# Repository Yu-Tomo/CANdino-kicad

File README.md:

# CANdino-kicad

CAN用IC搭載のArduino互換機になります。

Qiitaの記事はこちらから→https://qiita.com/Yu-Tomo/items/e30f2b3abf415f76f6f1

※基盤を発注は自己責任でお願いします。

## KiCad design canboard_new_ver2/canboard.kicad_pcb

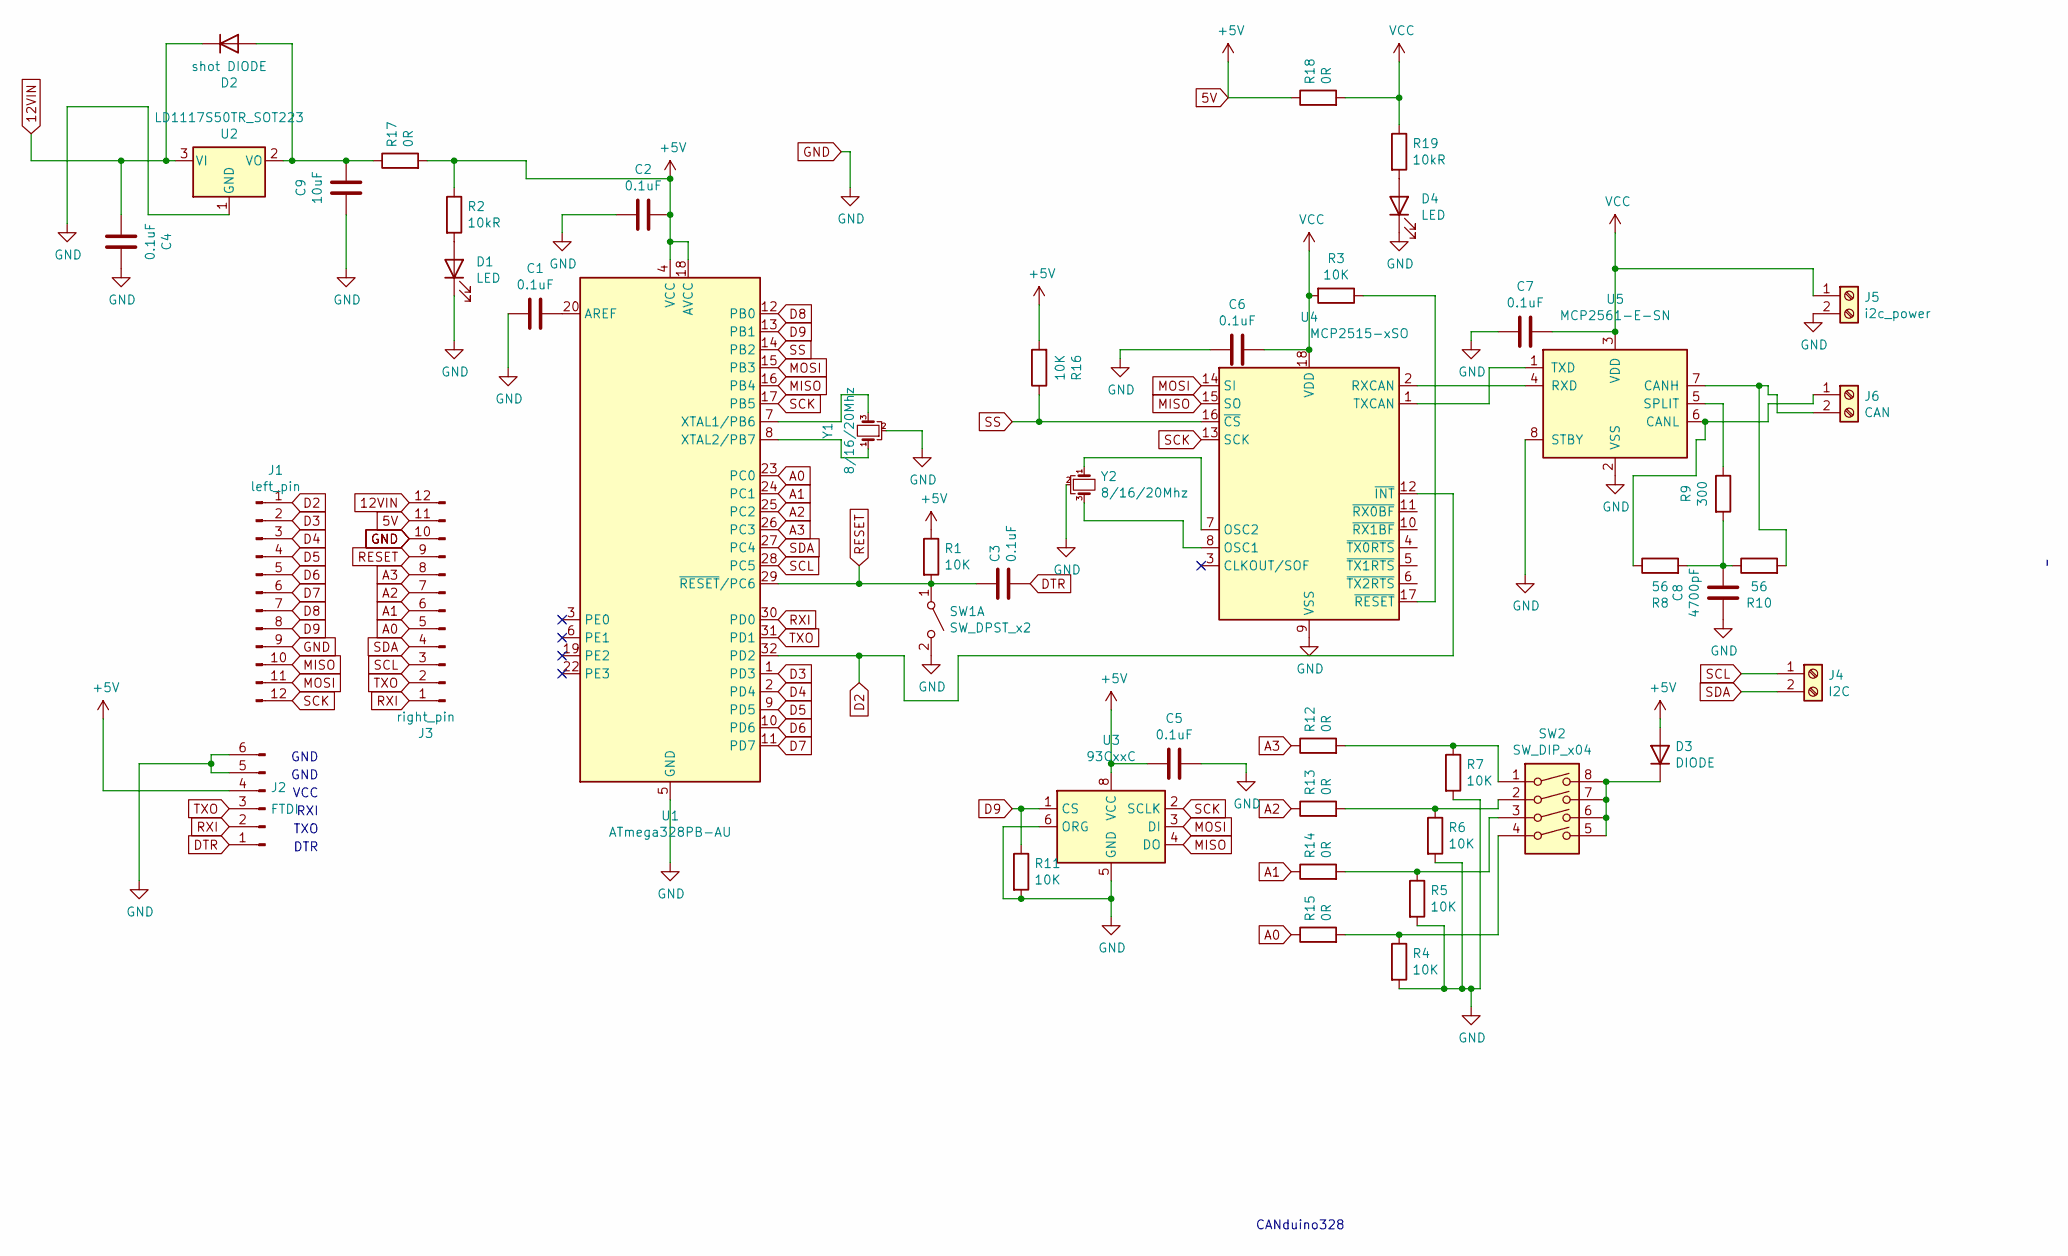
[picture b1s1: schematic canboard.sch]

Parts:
C1, C2, C3, C4, C5, C6, C7: 0.1uF; C_0402_1005Metric
C8: 4700pF; C_0603_1608Metric
C9: 10uF; C_0805_2012Metric
D1, D4: LED; LED_0603_1608Metric
D2: shot DIODE; D_0805_2012Metric
D3: DIODE; D_0805_2012Metric
J1: left_pin; PinHeader_1x12_P2.54mm_Vertical
J2: FTDI; PinHeader_1x06_P2.54mm_Vertical
J3: right_pin; PinHeader_1x12_P2.54mm_Vertical
J4: I2C; TerminalBlock_TE_282834-2_1x02_P2.54mm_Horizontal
J5: i2c_power; TerminalBlock_TE_282834-2_1x02_P2.54mm_Horizontal
J6: CAN; TerminalBlock_TE_282834-2_1x02_P2.54mm_Horizontal
R1, R3, R4, R5, R6, R7, R11, R16: 10K; R_0603_1608Metric
R2, R19: 10kR; R_0603_1608Metric
R8, R10: 56; R_1206_3216Metric
R9: 300; R_0603_1608Metric
R12, R13, R14, R15, R17, R18: 0R; R_0603_1608Metric
SW1: SW_DPST_x2; SW_SPST_REED_CT05-XXXX-J1
SW2: SW_DIP_x04; SW_DIP_SPSTx04_Slide_Copal_CHS-04B_W7.62mm_P1.27mm
U1: ATmega328PB-AU; TQFP-32_7x7mm_P0.8mm
U2: LD1117S50TR_SOT223; SOT-223-3_TabPin2
U3: 93CxxC; DIP-8_W7.62mm_Socket
U4: MCP2515-xSO; SOIC-18W_7.5x11.6mm_P1.27mm
U5: MCP2561-E-SN; SOIC-8_3.9x4.9mm_P1.27mm
Y1, Y2: 8/16/20Mhz; Resonator_SMD_muRata_CSTxExxV-3Pin_3.0x1.1mm_HandSoldering

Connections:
5V: C2.1, C5.2, D3.1 (A), J2.4, J3.11, R1.1, R2.1, R16.2, R17.2, R18.1, U1.4 (VCC), U1.18 (AVCC), U3.8 (VCC)
12VIN: C4.2, D2.2 (K), J3.12, U2.3 (VI)
A0: J3.5, R15.1, U1.23 (PC0)
A1: J3.6, R14.1, U1.24 (PC1)
A2: J3.7, R13.1, U1.25 (PC2)
A3: J3.8, R12.1, U1.26 (PC3)
D2: J1.1, U1.32 (PD2), U4.12 (~INT)
D3: J1.2, U1.1 (PD3)
D4: J1.3, U1.2 (PD4)
D5: J1.4, U1.9 (PD5)
D6: J1.5, U1.10 (PD6)
D7: J1.6, U1.11 (PD7)
D8: J1.7, U1.12 (PB0)
D9: J1.8, R11.1, U1.13 (PB1), U3.1 (CS)
DTR: C3.1, J2.1
GND: C1.2, C2.2, C4.1, C5.1, C6.2, C7.2, C8.2, C9.2, D1.1 (K), D4.1 (K), J1.9, J2.5, J2.6, J3.10, J5.2, R4.2, R5.2, R6.2, R7.2, R11.2, SW1.2 (B), U1.5 (GND), U1.21 (GND), U2.1 (GND), U3.5 (GND), U3.6 (ORG), U4.9 (VSS), U5.2 (VSS), U5.8 (STBY), Y1.2, Y2.2
MISO: J1.10, U1.16 (PB4), U3.4 (DO), U4.15 (SO)
MOSI: J1.11, U1.15 (PB3), U3.3 (DI), U4.14 (SI)
unnamed: C1.1, U1.20 (AREF)
unnamed: C8.1, R8.2, R9.2, R10.1
unnamed: C9.1, D2.1 (A), R17.1, U2.2 (VO)
unnamed: D1.2 (A), R2.2
unnamed: D3.2 (K), SW2.5, SW2.6, SW2.7, SW2.8
unnamed: D4.2 (A), R19.2
unnamed: J6.1, R8.1, U5.6 (CANL)
unnamed: J6.2, R10.2, U5.7 (CANH)
unnamed: R3.1, U4.17 (~RESET)
unnamed: R9.1, U5.5 (SPLIT)
unnamed: R7.1, R12.2, SW2.1
unnamed: R6.1, R13.2, SW2.2
unnamed: R5.1, R14.2, SW2.3
unnamed: R4.1, R15.2, SW2.4
unnamed: U1.7 (XTAL1/PB6), Y1.3
unnamed: U1.8 (XTAL2/PB7), Y1.1
unnamed: U4.1 (TXCAN), U5.1 (TXD)
unnamed: U4.2 (RXCAN), U5.4 (RXD)
unnamed: U4.7 (OSC2), Y2.1
unnamed: U4.8 (OSC1), Y2.3
RESET: C3.2, J3.9, R1.2, SW1.1 (A), U1.29 (~RESET~/PC6)
RXI: J2.2, J3.1, U1.30 (PD0)
SCK: J1.12, U1.17 (PB5), U3.2 (SCLK), U4.13 (SCK)
SCL: J3.3, J4.1, U1.28 (PC5)
SDA: J3.4, J4.2, U1.27 (PC4)
SS: R16.1, U1.14 (PB2), U4.16 (~CS)
TXO: J2.3, J3.2, U1.31 (PD1)
VCC: C6.1, C7.1, J5.1, R3.2, R18.2, R19.1, U4.18 (VDD), U5.3 (VDD)

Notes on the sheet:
GND
VCC
DTR
TXO
RXI
CANduino328

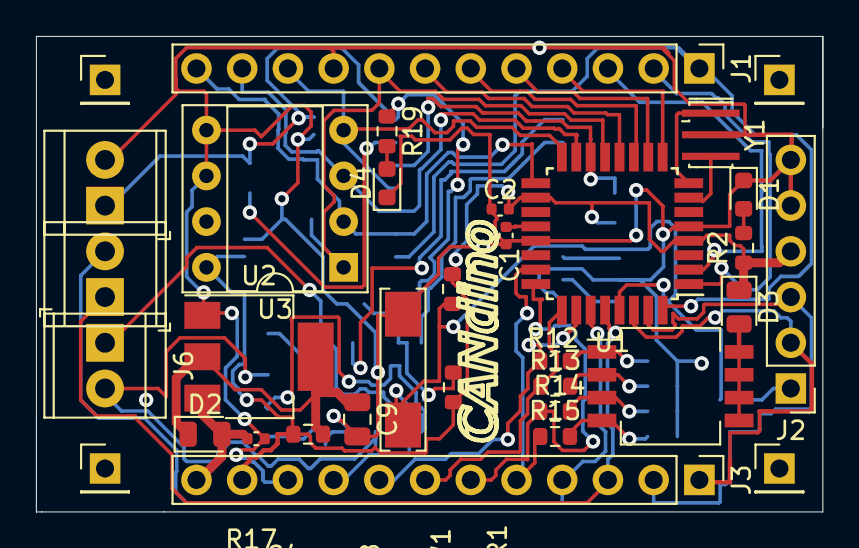
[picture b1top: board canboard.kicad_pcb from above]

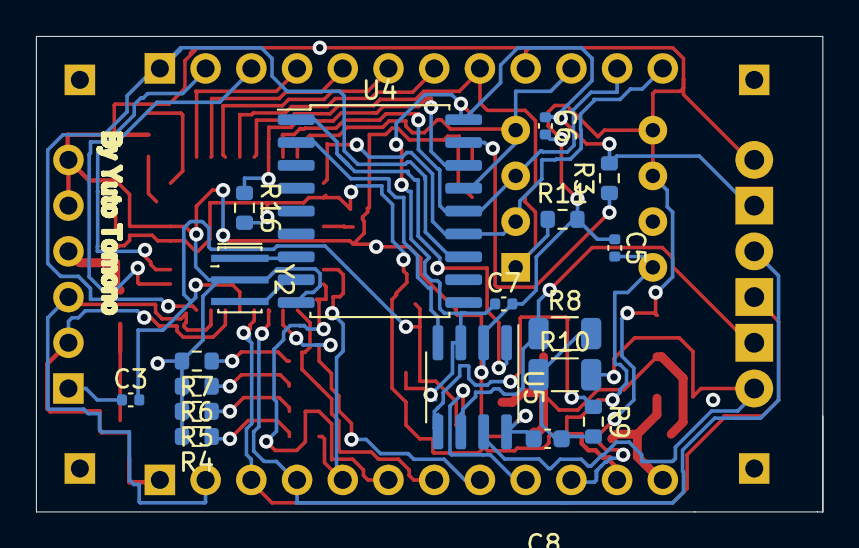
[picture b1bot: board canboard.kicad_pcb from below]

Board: 2 copper layers, 43.7 x 26.4 mm, 47 parts (18 on the bottom side), 46 nets.
